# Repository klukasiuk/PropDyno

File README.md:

# PropDyno

Micro UAV propeller meter

Features:
- thrust and torque readings
- voltage and amps readings
- step response analysis
- arduino nano based pcb
- using 3 load cells (12.7x12.7x80 up to 5 kg)
- HX711 modules with 80 Hz update rate
- external current meter and voltage divider
- PCB and STLs included

# Example readings

# Prototype

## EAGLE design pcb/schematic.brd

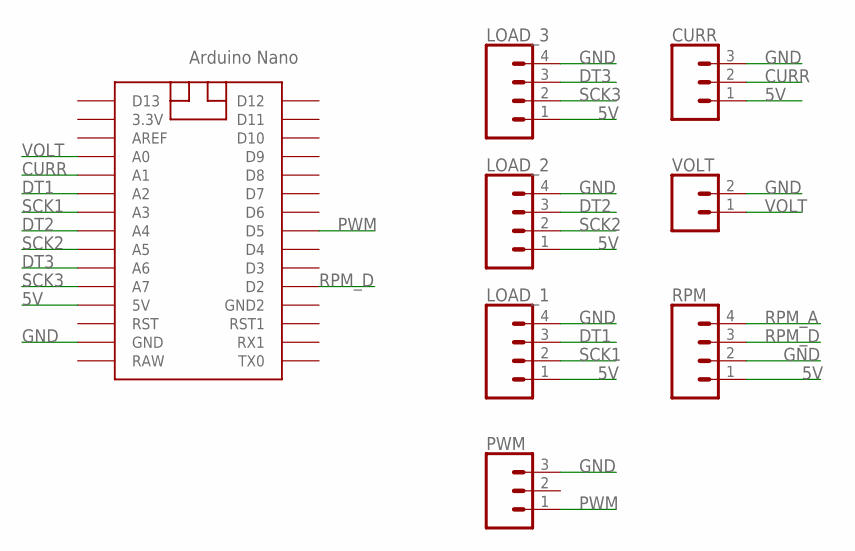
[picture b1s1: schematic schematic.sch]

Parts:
CURR: CONN_03POLAR; MOLEX-1X3
LOAD_1, LOAD_2, LOAD_3: CONN_04POLAR; MOLEX-1X4
PWM: CONN_03POLAR; MOLEX-1X3
RPM: CONN_04POLAR; MOLEX-1X4
U$1: NANO
VOLT: CONN_02POLAR; MOLEX-1X2

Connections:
5V: CURR.1, LOAD_1.1, LOAD_2.1, LOAD_3.1, RPM.1, U$1.5V
CURR: CURR.2, U$1.A1
DT1: LOAD_1.3, U$1.A2
DT2: LOAD_2.3, U$1.A4
DT3: LOAD_3.3, U$1.A6
GND: CURR.3, LOAD_1.4, LOAD_2.4, LOAD_3.4, PWM.3, RPM.2, U$1.GND, VOLT.2
PWM: PWM.1, U$1.D5
RPM_A: RPM.4
RPM_D: RPM.3, U$1.D2
SCK1: LOAD_1.2, U$1.A3
SCK2: LOAD_2.2, U$1.A5
SCK3: LOAD_3.2, U$1.A7
VOLT: U$1.A0, VOLT.1

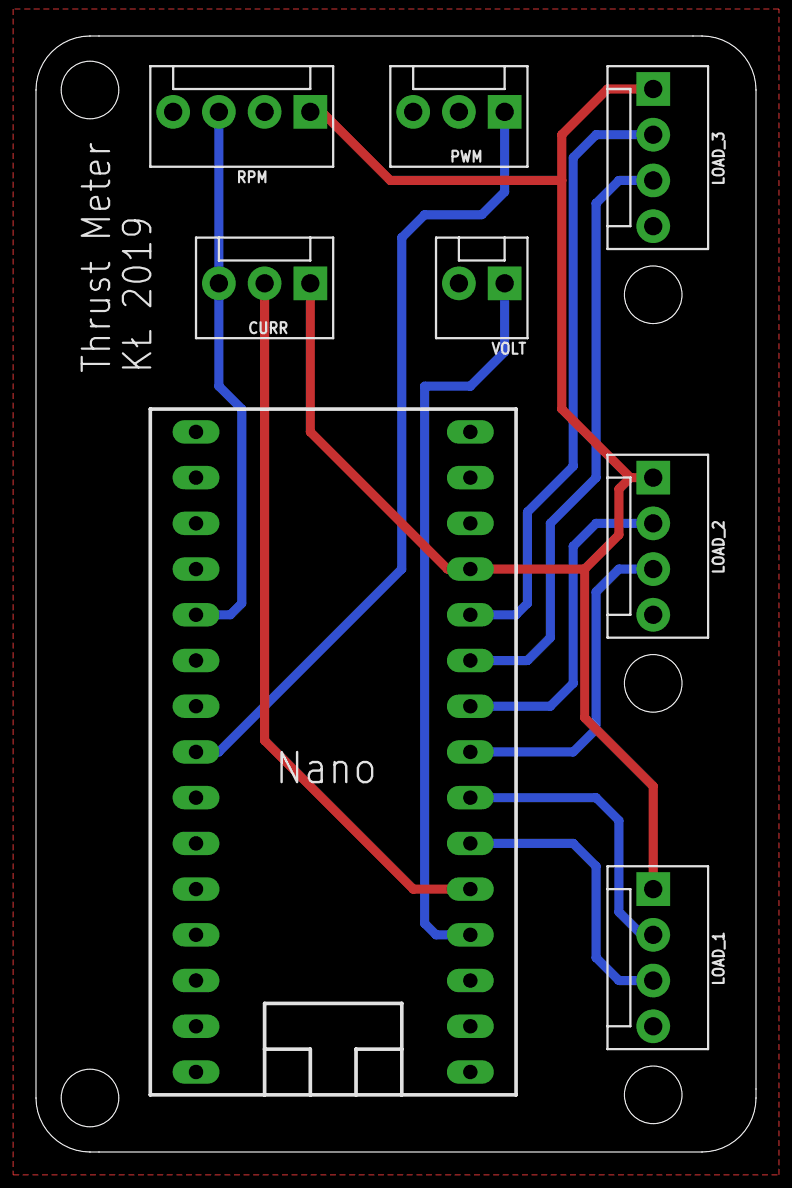
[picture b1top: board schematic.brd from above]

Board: 2 copper layers, 40.0 x 62.0 mm, 8 parts (0 on the bottom side), 12 nets.

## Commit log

2021-01-08 Upload files

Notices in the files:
parts and their libraries:
SparkFun-Connectors: Licensing: Creative Commons ShareAlike 4.0 International - https://creativecommons.org/licenses/by-sa/4.0
